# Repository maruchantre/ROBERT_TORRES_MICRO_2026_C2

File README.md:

Microcontroladores — Cuatrimestre 2, 2026

Nombre: Robert Torres
Carrera: Mecatrónica
Asignatura: Microcontroladores
Periodo académico: Cuatrimestre 2 del año 2026

Descripción

Este repositorio contiene las prácticas, tareas, códigos y proyectos desarrollados durante la asignatura de Microcontroladores.

El objetivo de este repositorio es documentar y organizar los trabajos realizados durante la materia, mostrando el progreso y los conocimientos adquiridos en programación, electrónica y sistemas embebidos.

Robert Torres
Estudiante de Mecatrónica
Cuatrimestre 2 — 2026

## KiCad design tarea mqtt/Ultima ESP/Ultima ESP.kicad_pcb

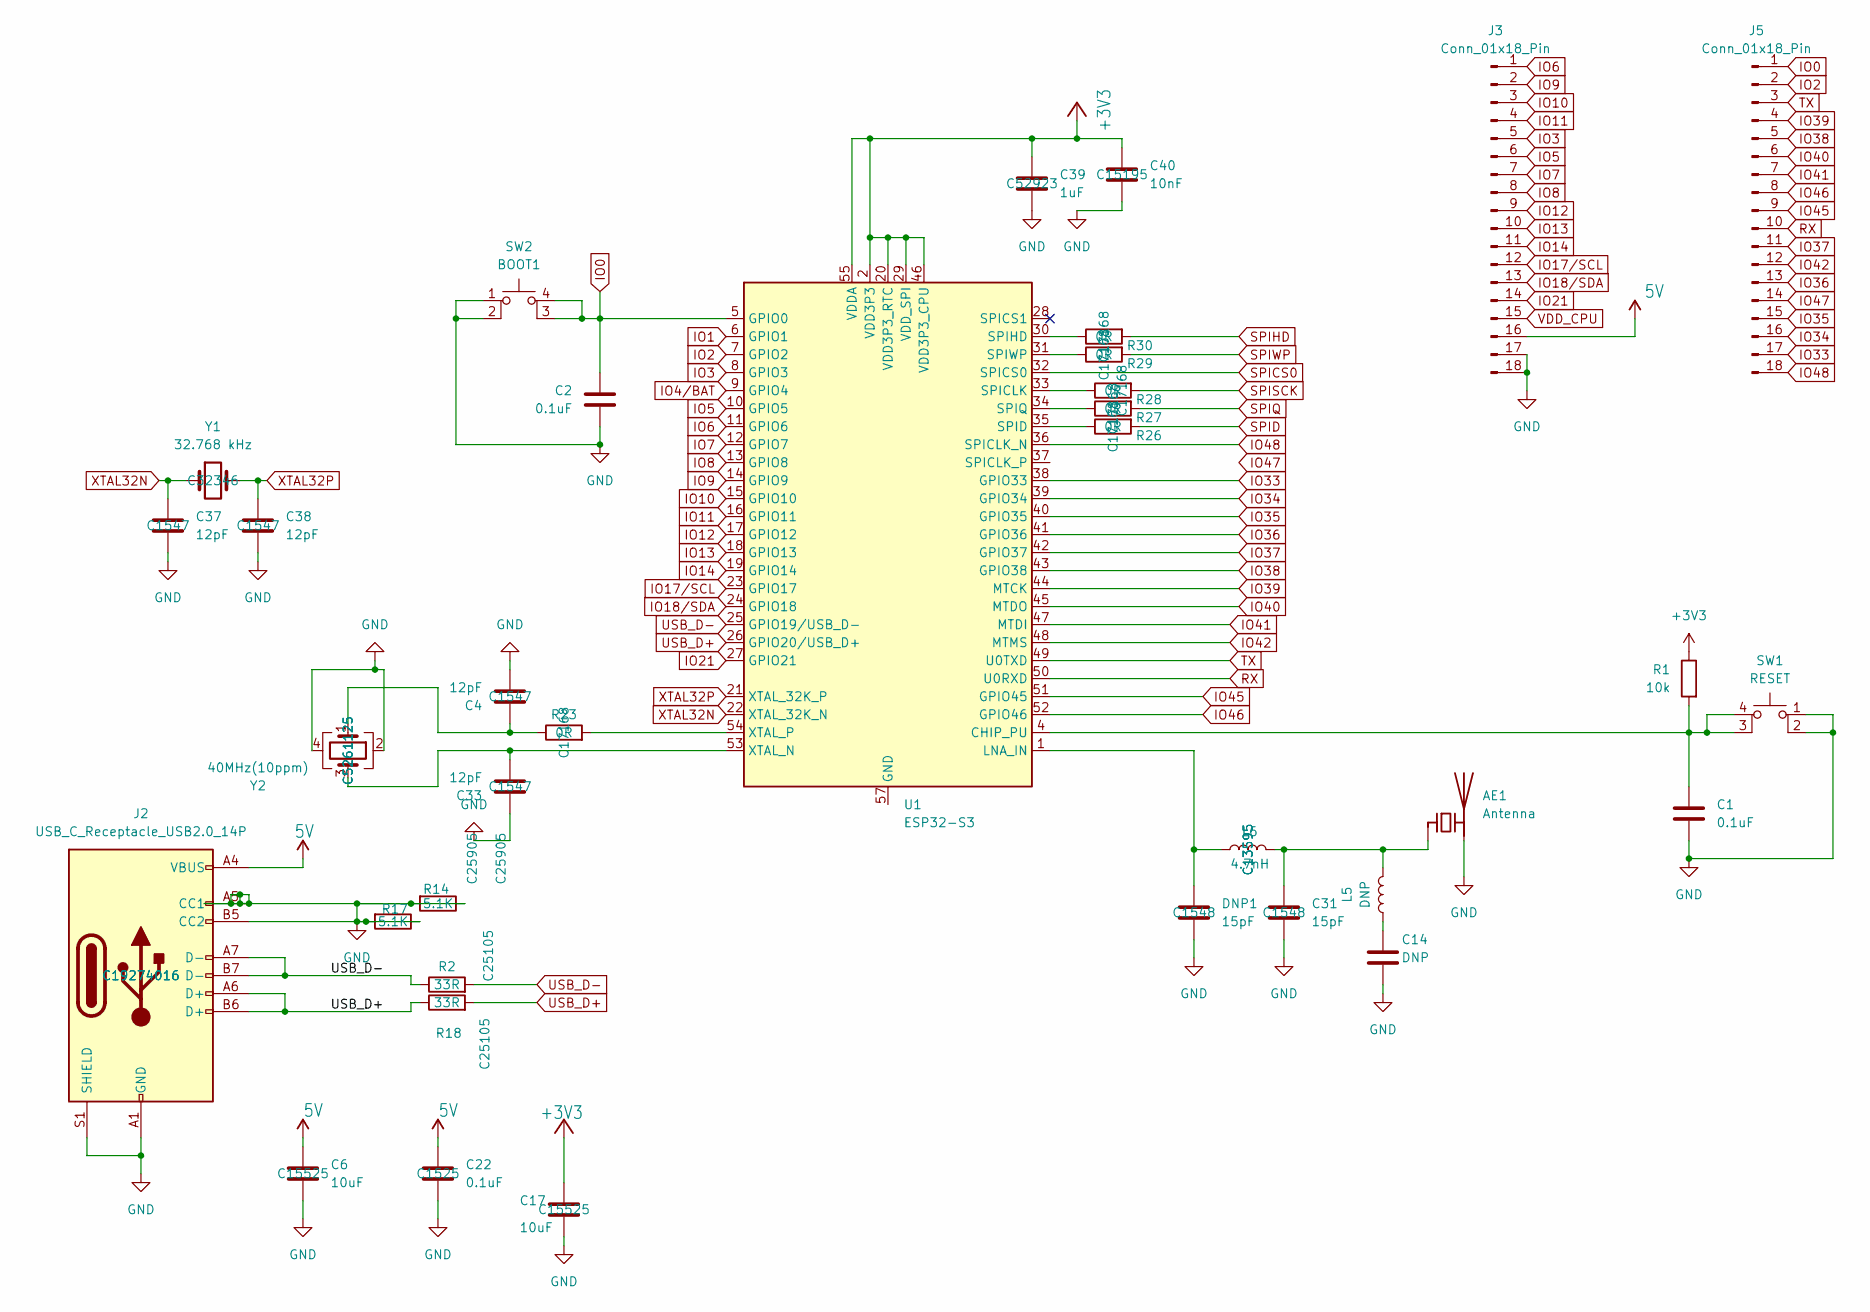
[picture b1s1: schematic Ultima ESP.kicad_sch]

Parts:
AE1: Antenna; Texas_SWRA117D_2.4GHz_Left
C1, C2: 0.1uF; C_0201_0603Metric
C4, C33, C37, C38: 12pF; C_0402_1005Metric; MNF PART NUMBER C1547; LCSC C1547
C6, C17: 10uF; C_0402_1005Metric; MNF PART NUMBER C15525; LCSC C15525
C14: DNP; C_0402_1005Metric
C22: 0.1uF; C_0402_1005Metric; MNF PART NUMBER C1525; LCSC C1525
C31: 15pF; C_0402_1005Metric; MNF PART NUMBER C1548; LCSC C1548
C39: 1uF; C_0402_1005Metric; MNF PART NUMBER C52923; LCSC C52923
C40: 10nF; C_0402_1005Metric; MNF PART NUMBER C15195; LCSC C15195
DNP1: 15pF; C_0402_1005Metric; MNF PART NUMBER C1548; LCSC C1548
J2: USB_C_Receptacle_USB2.0_14P; USB_C_Receptacle_HCTL_HC-TYPE-C-16P-01A; MNF PART NUMBER C19274016; LCSC C19274016
J3, J5: Conn_01x18_Pin; PinHeader_1x18_P2.54mm_Vertical
L5: DNP; L_0402_1005Metric
L6: 4.7nH; L_0402_1005Metric; MNF PART NUMBER C13595; LCSC C13595
R1: 10k
R2, R18: 33R; R_0402_1005Metric; MNF PART NUMBER C25105; LCSC C25105
R14, R17: 5.1K; R_0402_1005Metric; MNF PART NUMBER C25905; LCSC C25905
R23, R26, R27, R28, R29, R30: 0R; R_0402_1005Metric; MNF PART NUMBER C17168; LCSC C17168
SW1: RESET; SW_MEC_5GSH9
SW2: BOOT1; SW_MEC_5GSH9
U1: ESP32-S3; QFN-56-1EP_7x7mm_P0.4mm_EP4x4mm
Y1: 32.768 kHz; Crystal_SMD_3215-2Pin_3.2x1.5mm; MNF PART NUMBER C32346; LCSC C32346
Y2: 40MHz(10ppm); Crystal_SMD_2520-4Pin_2.5x2.0mm; MNF PART NUMBER C5261125; LCSC C5261125

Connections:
5V: C6.1, C22.1, J2.A4 (VBUS), J2.A9 (VBUS), J2.B4 (VBUS), J2.B9 (VBUS), J3.16
+3V3: C17.1, C39.1, C40.1, R1.1, U1.2 (VDD3P3), U1.3 (VDD3P3), U1.20 (VDD3P3_RTC), U1.29 (VDD_SPI), U1.46 (VDD3P3_CPU), U1.55 (VDDA), U1.56 (VDDA)
IO0: C2.1, J5.1, SW2.3 (K), SW2.4 (A), U1.5 (GPIO0)
IO1: U1.6 (GPIO1)
IO2: J5.2, U1.7 (GPIO2)
IO3: J3.5, U1.8 (GPIO3)
IO4/BAT: U1.9 (GPIO4)
IO5: J3.6, U1.10 (GPIO5)
IO6: J3.1, U1.11 (GPIO6)
IO7: J3.7, U1.12 (GPIO7)
IO8: J3.8, U1.13 (GPIO8)
IO9: J3.2, U1.14 (GPIO9)
IO10: J3.3, U1.15 (GPIO10)
IO11: J3.4, U1.16 (GPIO11)
IO12: J3.9, U1.17 (GPIO12)
IO13: J3.10, U1.18 (GPIO13)
IO14: J3.11, U1.19 (GPIO14)
IO17/SCL: J3.12, U1.23 (GPIO17)
IO18/SDA: J3.13, U1.24 (GPIO18)
IO21: J3.14, U1.27 (GPIO21)
IO33: J5.17, U1.38 (GPIO33)
IO34: J5.16, U1.39 (GPIO34)
IO35: J5.15, U1.40 (GPIO35)
IO36: J5.13, U1.41 (GPIO36)
IO37: J5.11, U1.42 (GPIO37)
IO38: J5.5, U1.43 (GPIO38)
IO39: J5.4, U1.44 (MTCK)
IO40: J5.6, U1.45 (MTDO)
IO41: J5.7, U1.47 (MTDI)
IO42: J5.12, U1.48 (MTMS)
IO45: J5.9, U1.51 (GPIO45)
IO46: J5.8, U1.52 (GPIO46)
IO47: J5.14
IO48: J5.18, U1.36 (SPICLK_N)
unnamed: AE1.1 (FEED), C31.1, L5.2, L6.2
unnamed: C4.1, R23.1, Y2.1
unnamed: C14.1, L5.1
unnamed: C1.1, R1.2, SW1.3 (K), SW1.4 (A), U1.4 (CHIP_PU)
unnamed: DNP1.1, L6.1, U1.1 (LNA_IN)
unnamed: R28.1, U1.33 (SPICLK)
unnamed: R26.1, U1.35 (SPID)
unnamed: R30.1, U1.30 (SPIHD)
unnamed: R27.1, U1.34 (SPIQ)
unnamed: R29.1, U1.31 (SPIWP)
unnamed: C33.2, U1.53 (XTAL_N), Y2.3
unnamed: R23.2, U1.54 (XTAL_P)
RX: J5.10, U1.50 (U0RXD)
SPICS0: U1.32 (SPICS0)
SPID: R26.2
SPIHD: R30.2
SPIQ: R27.2
SPISCK: R28.2
SPIWP: R29.2
USB_D+: J2.A6 (D+), J2.B6 (D+), R18.1, R18.2, U1.26 (GPIO20/USB_D+)
USB_D-: J2.A7 (D-), J2.B7 (D-), R2.1, R2.2, U1.25 (GPIO19/USB_D-)
VDD_CPU: J3.15
XTAL32N: C37.1, U1.22 (XTAL_32K_N), Y1.1
XTAL32P: C38.1, U1.21 (XTAL_32K_P), Y1.2

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
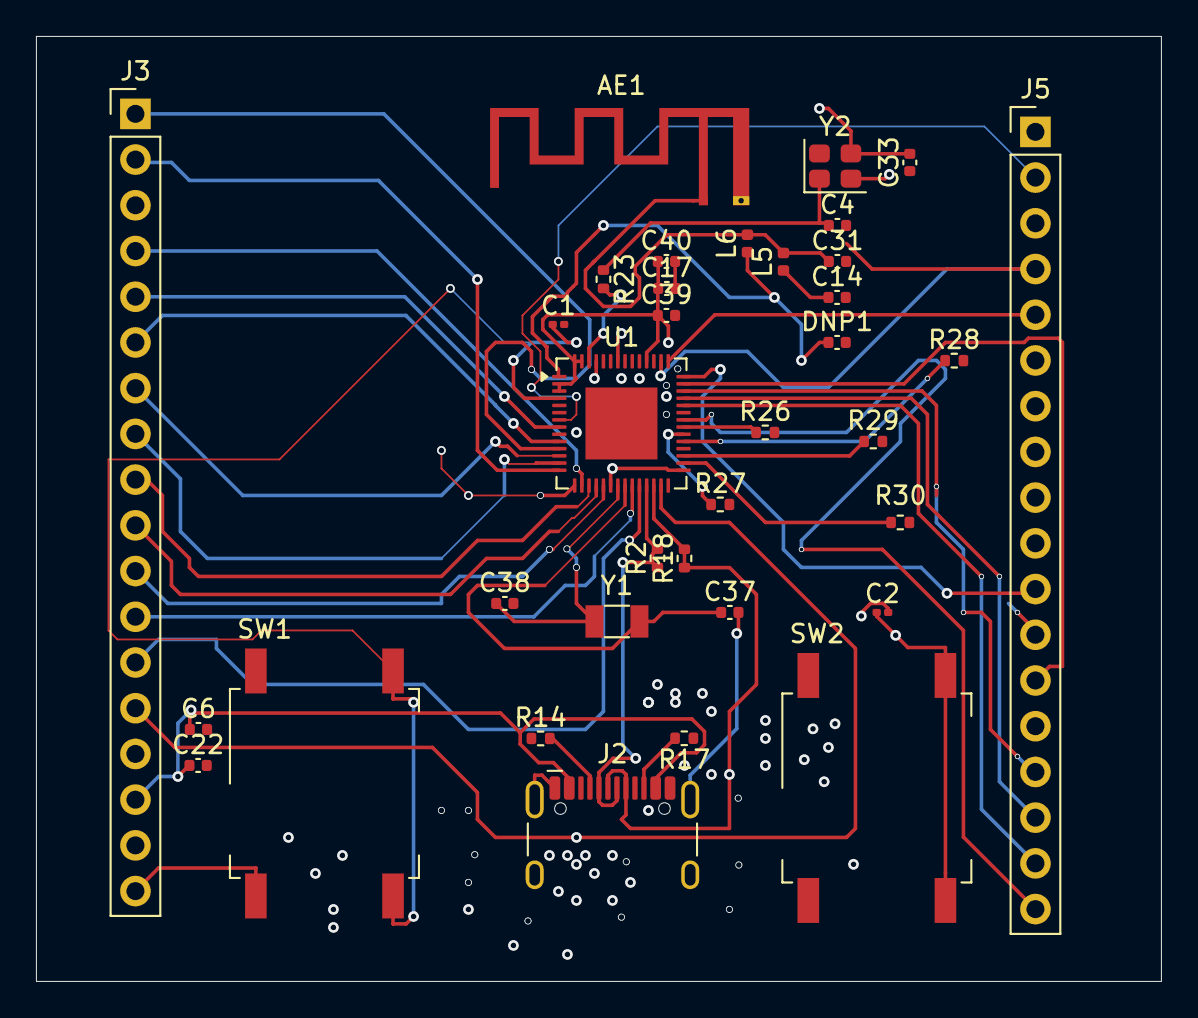
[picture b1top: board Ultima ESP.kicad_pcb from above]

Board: 4 copper layers, 62.5 x 52.5 mm, 35 parts (0 on the bottom side), 51 nets.

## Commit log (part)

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2026-06-11 TAREA 1
